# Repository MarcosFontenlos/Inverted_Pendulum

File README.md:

# Inverted Pendulum

Self-balancing two-wheeled robot built as the final project for the **Control Theory** course at the Universidade de Santiago de Compostela (2023/2024).

The robot keeps itself upright on two wheels by reading its tilt with an IMU and driving the motors through a PID controller. It also exposes a small Wi-Fi web interface that can be used to move it around or switch the controller on and off.

## How it works

1. **Sensing** - A MPU6050 IMU is read over I2C. The accelerometer gives an absolute (but noisy) tilt angle, while the gyroscope gives a fast (but drifting) angular rate.
2. **Angle estimation** - Both measurements are fused with a complementary filter:
   `angle = 0.98 * (angle + gyro_rate * dt) + 0.02 * accelerometer_angle`
   This yields a smooth and stable estimate of the tilt around the X axis.
3. **PID control** - The error is the difference between the desired angle (upright, 0 deg) and the measured angle. The output is:
   `u = Kp * error + Ki * integral + Kd * derivative`
   and is saturated to the PWM range (-255..255).
4. **Actuation** - The control signal is applied to both DC motors through a TB6612FNG driver. When the robot leans forward the wheels drive forward, and vice versa, producing the correction torque that brings it back to the vertical position.
5. **Tuning** - Gains are adjusted in the classic order: first `Kp`, then `Ki`, and finally `Kd` (in this build `Kd` was left at 0 because it did not improve the response).

The PID loop runs as fast as possible (small `delay`), since a high sampling rate is essential for balancing.

## Repository contents

| Path | Description |
| --- | --- |
| `Base_FreeCAD/` | FreeCAD models and STL files for the 3D-printed chassis. |
| `PCB/` | KiCad project (schematic, board layout, custom symbols/footprints), Gerber files and fabrication backups. |
| `Memoria/` | LaTeX report (`Memoria.tex` / `Memoria.pdf`) documenting the design, hardware and software. |
| `Programas/PID/` | Arduino sketches for the balancing controller: basic PID, low-pass filtered PID, IIR-filtered PID and PID with Wi-Fi position control. |
| `Programas/Programas_auxiliares/` | Helper sketches for motor testing, IMU measurements and sensor calibration. |
| `Prueba_esp32/` | Minimal sketch used to verify that the ESP32 board and toolchain work. |
| `Guion_proyecto.txt` | Short project log with the first hardware tests. |

## Hardware

- **ESP32** DevKit-C (main microcontroller, 5 V logic, built-in Wi-Fi).
- **MPU6050** (GY-521) accelerometer + gyroscope, I2C.
- **TB6612FNG** dual H-bridge motor driver.
- **2x DC gear motors** with wheels (ROB-14450).
- **2x 4xAA battery holders in series** (12 V for the motors) and an **LM7805** linear regulator (5 V for the ESP32).
- Custom PCB designed in KiCad and a 3D-printed base designed in FreeCAD.

> Note: the LM7805 needs at least ~7 V at its input, which is why the two 6 V battery packs are connected in series. The motors receive the full 12 V while the ESP32 is fed with regulated 5 V.

## Building and running

### Software

1. Install the **Arduino IDE** and add ESP32 board support through the Boards Manager.
2. Install the **MPU6050** and **I2Cdev** libraries.
3. Open one of the sketches in `Programas/` and select the ESP32 Dev Module board and the correct COM port.
4. Upload the sketch.

Recommended order for a first run:

1. `Prueba_esp32/` - check the board and serial connection.
2. `Programas/Programas_auxiliares/Programa_calibracion_sensor/` - calibrate the IMU offsets with the robot perfectly still.
3. `Programas/Programas_auxiliares/Marcha_motores/` - verify motor direction and wiring.
4. `Programas/PID/Control_PID/` - test and tune the PID.
5. `Programas/PID/PID_posicion/` - final version with Wi-Fi control.

### Wi-Fi control

`PID_posicion.ino` starts the ESP32 as a Wi-Fi access point. Connect to the network shown in the serial monitor and open the IP address (`192.168.4.1` by default) in a browser. The page provides forward/backward/left/right buttons, a stop button and buttons to enable or disable the PID.

The AP credentials are defined at the top of the sketch; change them before publishing or deploying the robot.

## Authors

- Marcos Fontenlos Ferreiro

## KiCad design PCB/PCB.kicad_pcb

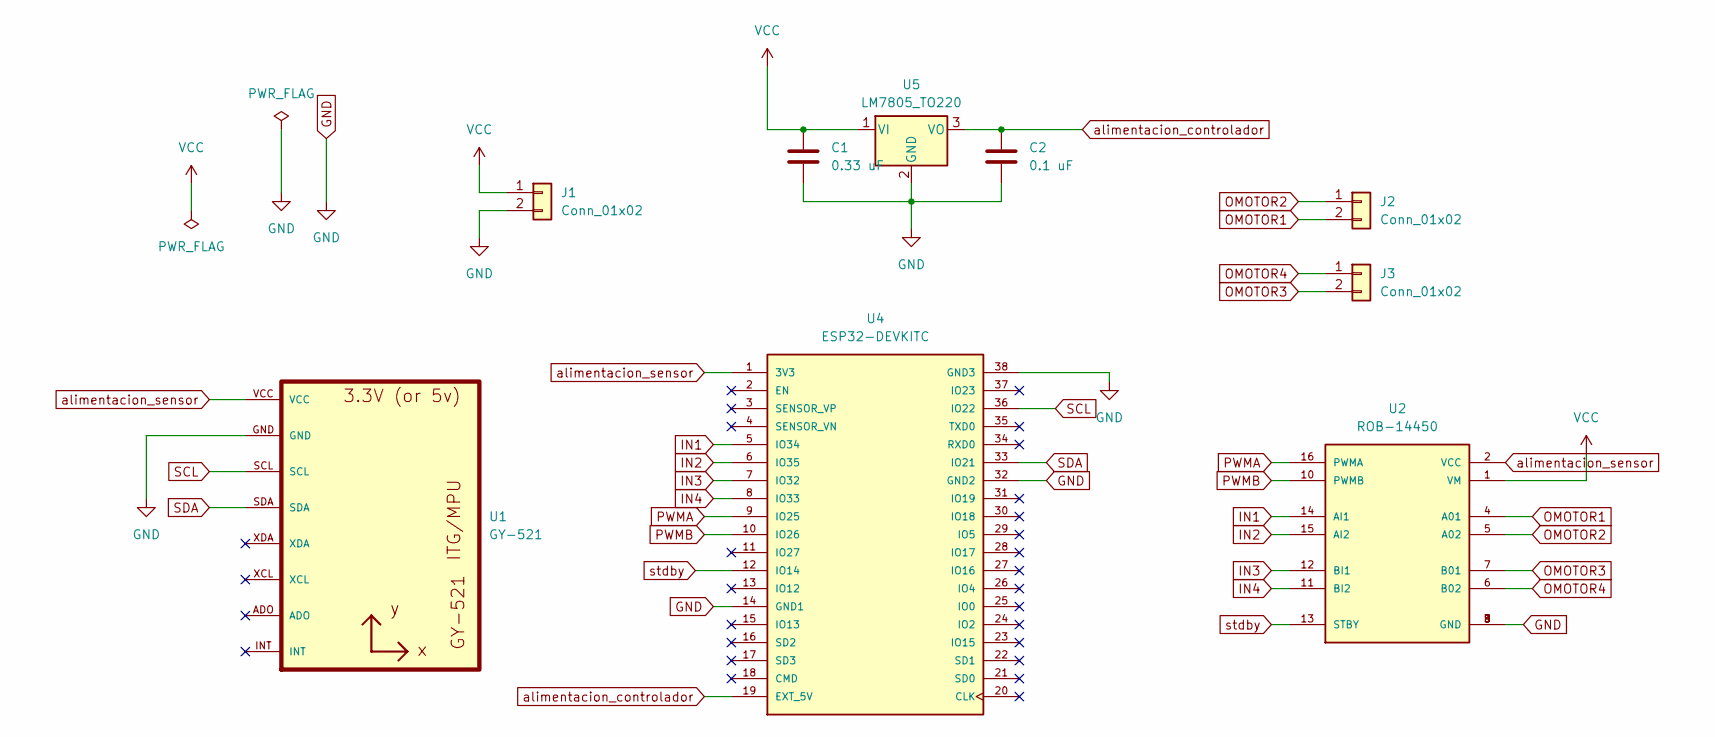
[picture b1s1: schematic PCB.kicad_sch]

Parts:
C1: 0.33 uF; C_Axial_L3.8mm_D2.6mm_P7.50mm_Horizontal
C2: 0.1 uF; C_Axial_L3.8mm_D2.6mm_P7.50mm_Horizontal
J1, J2, J3: Conn_01x02; PinSocket_1x02_P2.54mm_Vertical
U1: GY-521
U2: ROB-14450; MODULE_ROB-14450; PARTREV 11-13-17
U4: ESP32-DEVKITC; MODULE_ESP32-DEVKITC; PARTREV N/A
U5: LM7805_TO220; TO-220-3_Vertical

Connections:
GND: C1.2, C2.2, J1.2, U1.GND, U2.3 (GND), U2.8 (GND), U2.9 (GND), U4.14 (GND1), U4.32 (GND2), U4.38 (GND3), U5.2 (GND)
IN1: U2.14 (AI1), U4.5 (IO34)
IN2: U2.15 (AI2), U4.6 (IO35)
IN3: U2.12 (BI1), U4.7 (IO32)
IN4: U2.11 (BI2), U4.8 (IO33)
OMOTOR1: J2.2, U2.4 (A01)
OMOTOR2: J2.1, U2.5 (A02)
OMOTOR3: J3.2, U2.7 (B01)
OMOTOR4: J3.1, U2.6 (B02)
PWMA: U2.16 (PWMA), U4.9 (IO25)
PWMB: U2.10 (PWMB), U4.10 (IO26)
SCL: U1.SCL, U4.36 (IO22)
SDA: U1.SDA, U4.33 (IO21)
VCC: C1.1, J1.1, U2.1 (VM), U5.1 (VI)
alimentacion_controlador: C2.1, U4.19 (EXT_5V), U5.3 (VO)
alimentacion_sensor: U1.VCC, U2.2 (VCC), U4.1 (3V3)
stdby: U2.13 (STBY), U4.12 (IO14)

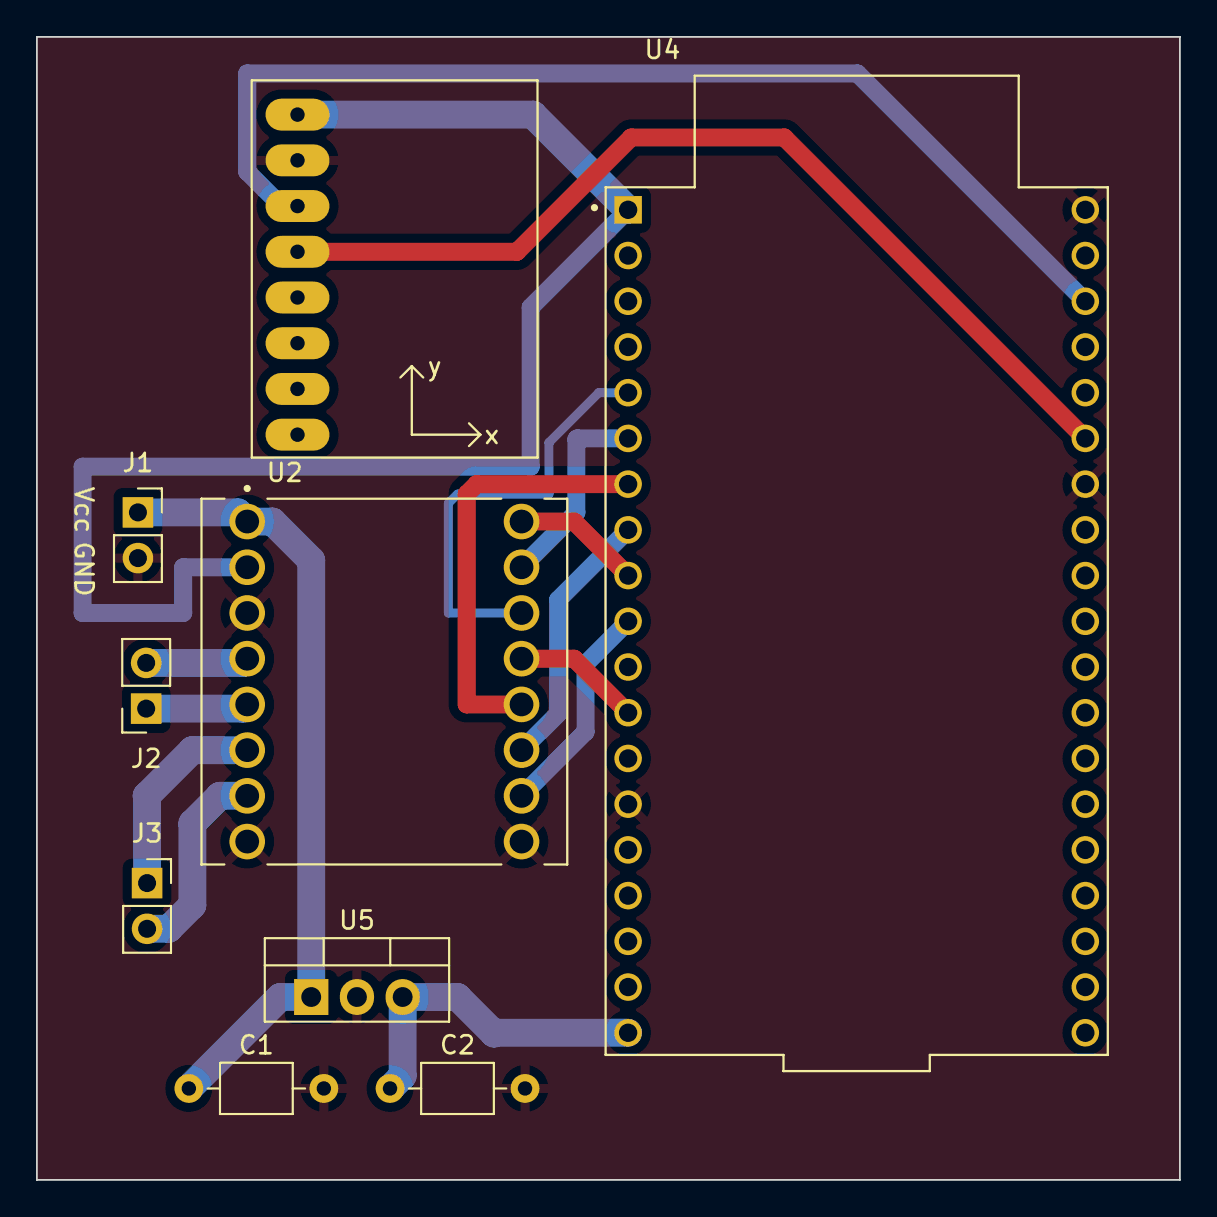
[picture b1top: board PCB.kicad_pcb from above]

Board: 2 copper layers, 63.5 x 63.5 mm, 9 parts (0 on the bottom side), 17 nets.
